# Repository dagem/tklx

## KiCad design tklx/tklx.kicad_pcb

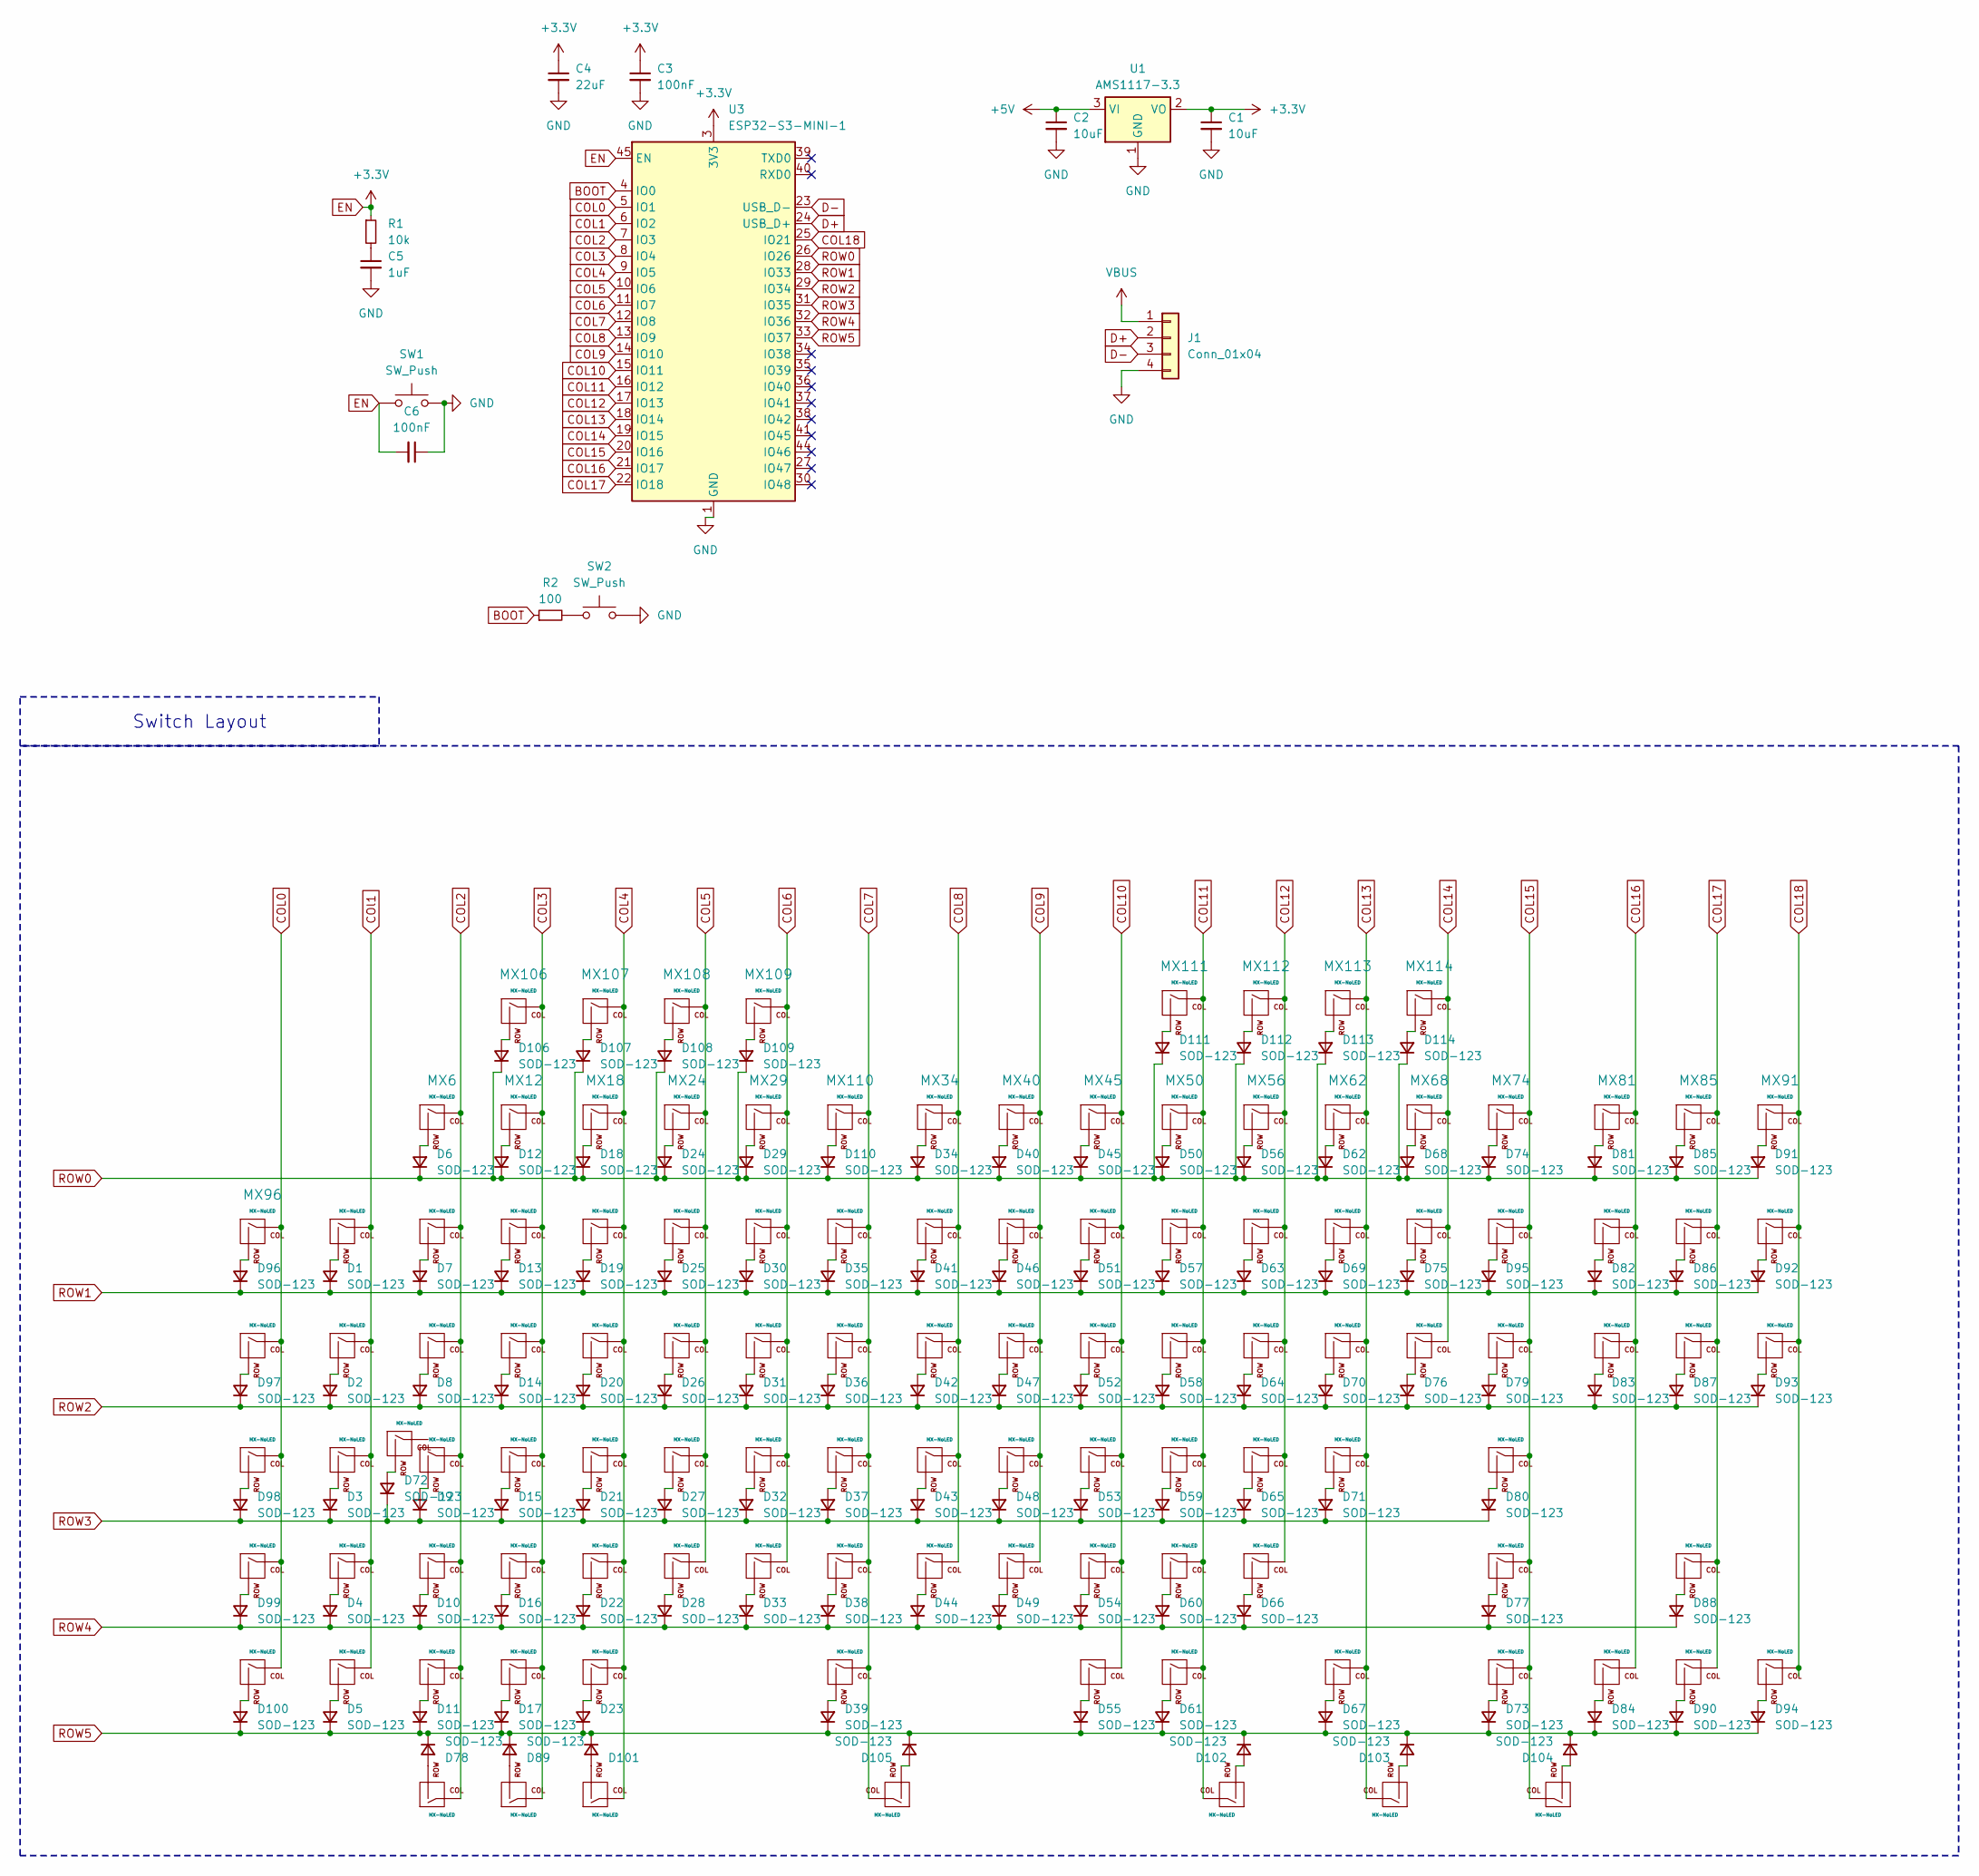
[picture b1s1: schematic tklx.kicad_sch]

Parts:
C1, C2: 10uF; C_0805_2012Metric
C3, C6: 100nF; C_0805_2012Metric
C4: 22uF; C_0805_2012Metric
C5: 1uF; C_0805_2012Metric
D1, D2, D3, D4, D5, D6, D7, D8, D9, D10, D11, D12, D13, D14, D15, D16, D17, D18, D19, D20, D21, D22, D23, D24, D25, D26, D27, D28, D29, D30, D31, D32, D33, D34, D35, D36, D37, D38, D39, D40, D41, D42, D43, D44, D45, D46, D47, D48, D49, D50, D51, D52, D53, D54, D55, D56, D57, D58, D59, D60, D61, D62, D63, D64, D65, D66, D67, D68, D69, D70, D71, D72, D73, D74, D75, D76, D77, D78, D79, D80, D81, D82, D83, D84, D85, D86, D87, D88, D89, D90, D91, D92, D93, D94, D95, D96, D97, D98, D99, D100, D101, D102, D103, D104, D105, D106, D107, D108, D109, D110, D111, D112, D113, D114: SOD-123; D_SOD-123
J1: Conn_01x04; JST_EH_S4B-EH_1x04_P2.50mm_Horizontal
MX1, MX2, MX3, MX4, MX5, MX6, MX7, MX12, MX13, MX14, MX15, MX16, MX18, MX19, MX20, MX21, MX22, MX24, MX25, MX26, MX27, MX28, MX29, MX30, MX31, MX32, MX33, MX34, MX35, MX36, MX37, MX38, MX40, MX41, MX42, MX43, MX44, MX45, MX46, MX47, MX48, MX49, MX50, MX51, MX52, MX53, MX54, MX56, MX57, MX58, MX59, MX60, MX62, MX63, MX64, MX65, MX66, MX68, MX69, MX70, MX71, MX74, MX75, MX76, MX81, MX82, MX83, MX84, MX85, MX86, MX87, MX88, MX89, MX90, MX91, MX92, MX93, MX94, MX96, MX97, MX98, MX99, MX100, MX103, MX106, MX107, MX108, MX109, MX110, MX111, MX112, MX113, MX114: MX-NoLED; MXOnly-1U-NoLED
MX8, MX78, MX79, MX101, MX102, MX104: MX-NoLED; MXOnly-1.5U-NoLED
MX9, MX72: MX-NoLED; MXOnly-1.75U-NoLED
MX10, MX80: MX-NoLED; MXOnly-2.25U-NoLED
MX11, MX17, MX23, MX55, MX61, MX67, MX73: MX-NoLED; MXOnly-1.25U-NoLED
MX39: MX-NoLED; MXOnly-6.25U-NoLED
MX77: MX-NoLED; MXOnly-2.75U-NoLED
MX95: MX-NoLED; MXOnly-2U-NoLED
MX105: MX-NoLED; MXOnly-7U-NoLED
R1: 10k; R_0805_2012Metric
R2: 100; R_0805_2012Metric
SW1, SW2: SW_Push; SW_Push_1P1T_XKB_TS-1187A
U1: AMS1117-3.3; SOT-223-3_TabPin2
U3: ESP32-S3-MINI-1; ESP32-S2-MINI-1

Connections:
+5V: C2.1, U1.3 (VI)
BOOT: R2.1, U3.4 (IO0)
COL0: MX96.1 (COL), MX97.1 (COL), MX98.1 (COL), MX99.1 (COL), MX100.1 (COL), U3.5 (IO1)
COL1: U3.6 (IO2)
COL2: MX6.1 (COL), MX7.1 (COL), MX8.1 (COL), MX9.1 (COL), MX10.1 (COL), MX11.1 (COL), MX78.1 (COL), U3.7 (IO3)
COL3: MX12.1 (COL), MX13.1 (COL), MX14.1 (COL), MX15.1 (COL), MX16.1 (COL), MX17.1 (COL), MX89.1 (COL), MX106.1 (COL), U3.8 (IO4)
COL4: MX18.1 (COL), MX19.1 (COL), MX20.1 (COL), MX21.1 (COL), MX22.1 (COL), MX23.1 (COL), MX101.1 (COL), MX107.1 (COL), U3.9 (IO5)
COL5: MX24.1 (COL), MX25.1 (COL), MX26.1 (COL), MX27.1 (COL), MX28.1 (COL), MX108.1 (COL), U3.10 (IO6)
COL6: MX29.1 (COL), MX30.1 (COL), MX31.1 (COL), MX32.1 (COL), MX33.1 (COL), MX109.1 (COL), U3.11 (IO7)
COL7: MX35.1 (COL), MX36.1 (COL), MX37.1 (COL), MX38.1 (COL), MX39.1 (COL), MX105.1 (COL), MX110.1 (COL), U3.12 (IO8)
COL8: MX34.1 (COL), MX41.1 (COL), MX42.1 (COL), MX43.1 (COL), MX44.1 (COL), U3.13 (IO9)
COL9: MX40.1 (COL), MX46.1 (COL), MX47.1 (COL), MX48.1 (COL), MX49.1 (COL), U3.14 (IO10)
COL10: MX45.1 (COL), MX51.1 (COL), MX52.1 (COL), MX53.1 (COL), MX54.1 (COL), MX55.1 (COL), U3.15 (IO11)
COL11: MX50.1 (COL), MX57.1 (COL), MX58.1 (COL), MX59.1 (COL), MX60.1 (COL), MX61.1 (COL), MX102.1 (COL), MX111.1 (COL), U3.16 (IO12)
COL12: MX56.1 (COL), MX63.1 (COL), MX64.1 (COL), MX65.1 (COL), MX66.1 (COL), MX112.1 (COL), U3.17 (IO13)
COL13: MX62.1 (COL), MX67.1 (COL), MX69.1 (COL), MX70.1 (COL), MX71.1 (COL), MX103.1 (COL), MX113.1 (COL), U3.18 (IO14)
COL14: MX68.1 (COL), MX75.1 (COL), MX76.1 (COL), MX114.1 (COL), U3.19 (IO15)
COL15: MX73.1 (COL), MX74.1 (COL), MX77.1 (COL), MX79.1 (COL), MX80.1 (COL), MX95.1 (COL), MX104.1 (COL), U3.20 (IO16)
COL16: MX81.1 (COL), MX82.1 (COL), MX83.1 (COL), MX84.1 (COL), U3.21 (IO17)
COL17: MX85.1 (COL), MX86.1 (COL), MX87.1 (COL), MX88.1 (COL), MX90.1 (COL), U3.22 (IO18)
COL18: MX91.1 (COL), MX92.1 (COL), MX93.1 (COL), MX94.1 (COL), U3.25 (IO21)
COl1: MX1.1 (COL), MX2.1 (COL), MX3.1 (COL), MX4.1 (COL), MX5.1 (COL)
D+: J1.2, U3.24 (USB_D+)
D-: J1.3, U3.23 (USB_D-)
EN: C1.1, C3.1, C4.1, C6.2, R1.1, SW1.1, U1.2 (VO), U3.3 (3V3), U3.45 (EN)
GND: C1.2, C2.2, C3.2, C4.2, C5.2, C6.1, J1.4, SW1.2, SW2.2, U1.1 (GND), U3.1 (GND), U3.2 (GND), U3.42 (GND), U3.43 (GND), U3.46 (GND), U3.47 (GND), U3.48 (GND), U3.49 (GND), U3.50 (GND), U3.51 (GND), U3.52 (GND), U3.53 (GND), U3.54 (GND), U3.55 (GND), U3.56 (GND), U3.57 (GND), U3.58 (GND), U3.59 (GND), U3.60 (GND), U3.61 (GND), U3.62 (GND), U3.63 (GND), U3.64 (GND), U3.65 (GND)
unnamed: C5.1, R1.2
unnamed: D1.2 (A), MX1.2 (ROW)
unnamed: D2.2 (A), MX2.2 (ROW)
unnamed: D3.2 (A), MX3.2 (ROW)
unnamed: D4.2 (A), MX4.2 (ROW)
unnamed: D5.2 (A), MX5.2 (ROW)
unnamed: D6.2 (A), MX6.2 (ROW)
unnamed: D7.2 (A), MX7.2 (ROW)
unnamed: D8.2 (A), MX8.2 (ROW)
unnamed: D9.2 (A), MX9.2 (ROW)
unnamed: D10.2 (A), MX10.2 (ROW)
unnamed: D11.2 (A), MX11.2 (ROW)
unnamed: D12.2 (A), MX12.2 (ROW)
unnamed: D13.2 (A), MX13.2 (ROW)
unnamed: D14.2 (A), MX14.2 (ROW)
unnamed: D15.2 (A), MX15.2 (ROW)
unnamed: D16.2 (A), MX16.2 (ROW)
unnamed: D17.2 (A), MX17.2 (ROW)
unnamed: D18.2 (A), MX18.2 (ROW)
unnamed: D19.2 (A), MX19.2 (ROW)
unnamed: D20.2 (A), MX20.2 (ROW)
unnamed: D21.2 (A), MX21.2 (ROW)
unnamed: D22.2 (A), MX22.2 (ROW)
unnamed: D23.2 (A), MX23.2 (ROW)
unnamed: D24.2 (A), MX24.2 (ROW)
unnamed: D25.2 (A), MX25.2 (ROW)
unnamed: D26.2 (A), MX26.2 (ROW)
unnamed: D27.2 (A), MX27.2 (ROW)
unnamed: D28.2 (A), MX28.2 (ROW)
unnamed: D29.2 (A), MX29.2 (ROW)
unnamed: D30.2 (A), MX30.2 (ROW)
unnamed: D31.2 (A), MX31.2 (ROW)
unnamed: D32.2 (A), MX32.2 (ROW)
unnamed: D33.2 (A), MX33.2 (ROW)
unnamed: D34.2 (A), MX34.2 (ROW)
unnamed: D35.2 (A), MX35.2 (ROW)
unnamed: D36.2 (A), MX36.2 (ROW)
unnamed: D37.2 (A), MX37.2 (ROW)
unnamed: D38.2 (A), MX38.2 (ROW)
unnamed: D39.2 (A), MX39.2 (ROW)
unnamed: D40.2 (A), MX40.2 (ROW)
unnamed: D41.2 (A), MX41.2 (ROW)
unnamed: D42.2 (A), MX42.2 (ROW)
unnamed: D43.2 (A), MX43.2 (ROW)
unnamed: D44.2 (A), MX44.2 (ROW)
unnamed: D45.2 (A), MX45.2 (ROW)
unnamed: D46.2 (A), MX46.2 (ROW)
unnamed: D47.2 (A), MX47.2 (ROW)
unnamed: D48.2 (A), MX48.2 (ROW)
unnamed: D49.2 (A), MX49.2 (ROW)
unnamed: D50.2 (A), MX50.2 (ROW)
unnamed: D51.2 (A), MX51.2 (ROW)
unnamed: D52.2 (A), MX52.2 (ROW)
unnamed: D53.2 (A), MX53.2 (ROW)
unnamed: D54.2 (A), MX54.2 (ROW)
unnamed: D55.2 (A), MX55.2 (ROW)
unnamed: D56.2 (A), MX56.2 (ROW)
unnamed: D57.2 (A), MX57.2 (ROW)
unnamed: D58.2 (A), MX58.2 (ROW)
unnamed: D59.2 (A), MX59.2 (ROW)
unnamed: D60.2 (A), MX60.2 (ROW)
unnamed: D61.2 (A), MX61.2 (ROW)
unnamed: D62.2 (A), MX62.2 (ROW)
unnamed: D63.2 (A), MX63.2 (ROW)
unnamed: D64.2 (A), MX64.2 (ROW)
unnamed: D65.2 (A), MX65.2 (ROW)
unnamed: D66.2 (A), MX66.2 (ROW)
unnamed: D67.2 (A), MX67.2 (ROW)
unnamed: D68.2 (A), MX68.2 (ROW)
unnamed: D69.2 (A), MX69.2 (ROW)
unnamed: D70.2 (A), MX70.2 (ROW)
unnamed: D71.2 (A), MX71.2 (ROW)
unnamed: D72.2 (A), MX72.2 (ROW)
unnamed: D73.2 (A), MX73.2 (ROW)
unnamed: D74.2 (A), MX74.2 (ROW)
unnamed: D75.2 (A), MX75.2 (ROW)
unnamed: D76.2 (A), MX76.2 (ROW)
unnamed: D77.2 (A), MX77.2 (ROW)
unnamed: D78.2 (A), MX78.2 (ROW)
unnamed: D79.2 (A), MX79.2 (ROW)
unnamed: D80.2 (A), MX80.2 (ROW)
unnamed: D81.2 (A), MX81.2 (ROW)
unnamed: D82.2 (A), MX82.2 (ROW)
unnamed: D83.2 (A), MX83.2 (ROW)
unnamed: D84.2 (A), MX84.2 (ROW)
unnamed: D85.2 (A), MX85.2 (ROW)
unnamed: D86.2 (A), MX86.2 (ROW)
unnamed: D87.2 (A), MX87.2 (ROW)
unnamed: D88.2 (A), MX88.2 (ROW)
unnamed: D89.2 (A), MX89.2 (ROW)
unnamed: D90.2 (A), MX90.2 (ROW)
unnamed: D91.2 (A), MX91.2 (ROW)
unnamed: D92.2 (A), MX92.2 (ROW)
unnamed: D93.2 (A), MX93.2 (ROW)
unnamed: D94.2 (A), MX94.2 (ROW)
unnamed: D95.2 (A), MX95.2 (ROW)
unnamed: D96.2 (A), MX96.2 (ROW)
unnamed: D97.2 (A), MX97.2 (ROW)
unnamed: D98.2 (A), MX98.2 (ROW)
unnamed: D99.2 (A), MX99.2 (ROW)
unnamed: D100.2 (A), MX100.2 (ROW)
unnamed: D101.2 (A), MX101.2 (ROW)
unnamed: D102.2 (A), MX102.2 (ROW)
unnamed: D103.2 (A), MX103.2 (ROW)
unnamed: D104.2 (A), MX104.2 (ROW)
unnamed: D105.2 (A), MX105.2 (ROW)
unnamed: D106.2 (A), MX106.2 (ROW)
unnamed: D107.2 (A), MX107.2 (ROW)
unnamed: D108.2 (A), MX108.2 (ROW)
unnamed: D109.2 (A), MX109.2 (ROW)
unnamed: D110.2 (A), MX110.2 (ROW)
unnamed: D111.2 (A), MX111.2 (ROW)
unnamed: D112.2 (A), MX112.2 (ROW)
unnamed: D113.2 (A), MX113.2 (ROW)
unnamed: D114.2 (A), MX114.2 (ROW)
unnamed: R2.2, SW2.1
ROW0: D6.1 (K), D12.1 (K), D18.1 (K), D24.1 (K), D29.1 (K), D34.1 (K), D40.1 (K), D45.1 (K), D50.1 (K), D56.1 (K), D62.1 (K), D68.1 (K), D74.1 (K), D81.1 (K), D85.1 (K), D91.1 (K), D106.1 (K), D107.1 (K), D108.1 (K), D109.1 (K), D110.1 (K), D111.1 (K), D112.1 (K), D113.1 (K), D114.1 (K), U3.26 (IO26)
ROW1: D1.1 (K), D7.1 (K), D13.1 (K), D19.1 (K), D25.1 (K), D30.1 (K), D35.1 (K), D41.1 (K), D46.1 (K), D51.1 (K), D57.1 (K), D63.1 (K), D69.1 (K), D75.1 (K), D82.1 (K), D86.1 (K), D92.1 (K), D95.1 (K), D96.1 (K), U3.28 (IO33)
ROW2: D2.1 (K), D8.1 (K), D14.1 (K), D20.1 (K), D26.1 (K), D31.1 (K), D36.1 (K), D42.1 (K), D47.1 (K), D52.1 (K), D58.1 (K), D64.1 (K), D70.1 (K), D76.1 (K), D79.1 (K), D83.1 (K), D87.1 (K), D93.1 (K), D97.1 (K), U3.29 (IO34)
ROW3: D3.1 (K), D9.1 (K), D15.1 (K), D21.1 (K), D27.1 (K), D32.1 (K), D37.1 (K), D43.1 (K), D48.1 (K), D53.1 (K), D59.1 (K), D65.1 (K), D71.1 (K), D72.1 (K), D80.1 (K), D98.1 (K), U3.31 (IO35)
ROW4: D4.1 (K), D10.1 (K), D16.1 (K), D22.1 (K), D28.1 (K), D33.1 (K), D38.1 (K), D44.1 (K), D49.1 (K), D54.1 (K), D60.1 (K), D66.1 (K), D77.1 (K), D88.1 (K), D99.1 (K), U3.32 (IO36)
ROW5: D5.1 (K), D11.1 (K), D17.1 (K), D23.1 (K), D39.1 (K), D55.1 (K), D61.1 (K), D67.1 (K), D73.1 (K), D78.1 (K), D84.1 (K), D89.1 (K), D90.1 (K), D94.1 (K), D100.1 (K), D101.1 (K), D102.1 (K), D103.1 (K), D104.1 (K), D105.1 (K), U3.33 (IO37)
VBUS: J1.1

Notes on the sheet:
Switch Layout

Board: 2 copper layers, 241 parts (127 on the bottom side), 147 nets, no tracks yet.

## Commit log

2024-12-31 added submodules
2024-12-31 created kicad files
2024-12-31 finished wiring for switches
2025-01-24 finished keyswitch layout
2025-01-29 finished microcontroller layout
2025-01-29 added support for 7u and stepped caps
2025-01-31 placed diodes
2025-01-31 finished diode layout
2025-01-31 flipped keys for tsangan layout to be on correct plane
2025-02-01 rotated keys for tsangan layout and stepped caps to be proper orientation.
2025-02-01 added support for f13 row
2025-02-03 intial stm32 design
2025-02-05 finished esp32 wireless design
2025-02-07 prelim esp32-mini design
